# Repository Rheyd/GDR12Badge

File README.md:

# GDR12Badge
GDR Guerra de Robots badge
Now with Pinout Card :D
The GDR12 folder already contains all the example codes up-to-date, this examples will be inmproved over time, and if you spoot a problem please tell me, and also i'll upload more codes, if you have a request, then tell me :D

if you're interested in the procees you can see the post over hackaday, or twitter

https://hackaday.io/project/159659-guerra-de-robots-robots-war-official-badge

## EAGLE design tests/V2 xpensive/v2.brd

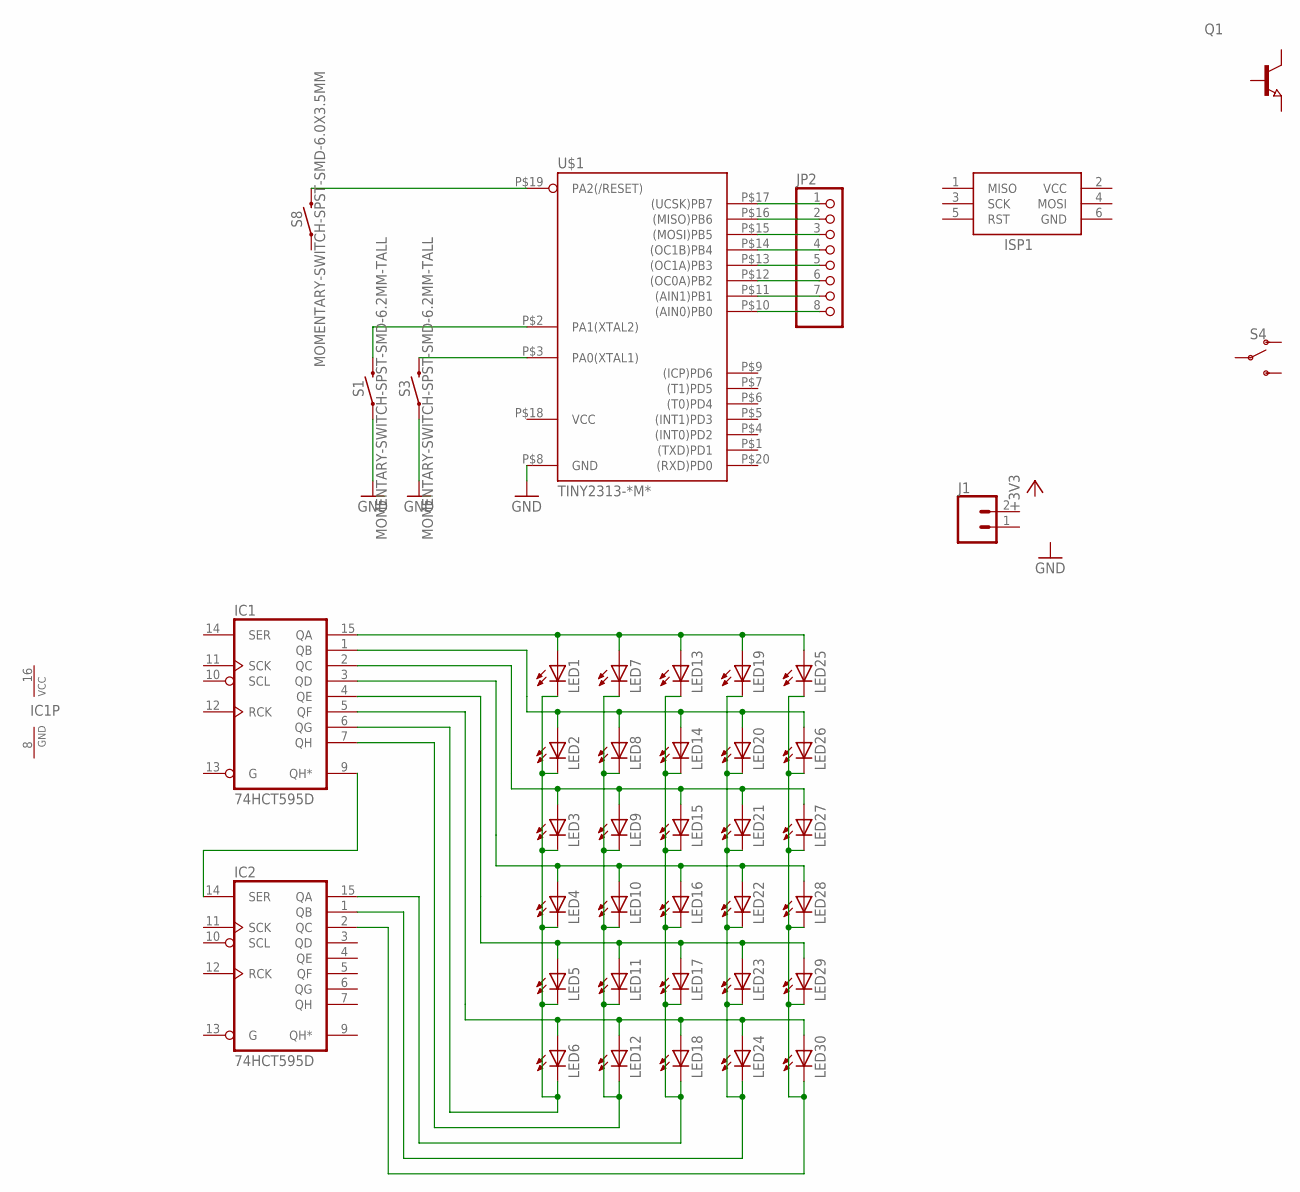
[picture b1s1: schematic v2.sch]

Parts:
IC1, IC2: 74HCT595D; SO16
ISP1: AVRISP-6; AVRISP
J1: CONN_02; 1X02
JP2: PINHD-1X8BIG; 1X08-BIG
LED1, LED2, LED3, LED4, LED5, LED6, LED7, LED8, LED9, LED10, LED11, LED12, LED13, LED14, LED15, LED16, LED17, LED18, LED19, LED20, LED21, LED22, LED23, LED24, LED25, LED26, LED27, LED28, LED29, LED30: LEDCHIPLED_1206; CHIPLED_1206
Q1: NPN-TRANSISTOR_SOT23; SOT23
S1, S3: MOMENTARY-SWITCH-SPST-SMD-6.2MM-TALL; TACTILE_SWITCH_SMD_6.2MM_TALL
S4: SWITCH-SPDT-SMD-RIGHT-ANGLE; SWITCH_SPST_SMD_A
S8: MOMENTARY-SWITCH-SPST-SMD-6.0X3.5MM; TACTILE_SWITCH_SMD_6.0X3.5MM
U$1: TINY2313-*M*; MLF20

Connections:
GND: IC1.8 (GND), IC2.8 (GND), ISP1.6 (GND), S1.A2 (1), S3.A2 (1), U$1.P$8 (GND)
unnamed: JP2.1, U$1.P$17 ((UCSK)PB7)
unnamed: JP2.2, U$1.P$16 ((MISO)PB6)
unnamed: JP2.3, U$1.P$15 ((MOSI)PB5)
unnamed: JP2.4, U$1.P$14 ((OC1B)PB4)
unnamed: JP2.5, U$1.P$13 ((OC1A)PB3)
unnamed: JP2.6, U$1.P$12 ((OC0A)PB2)
unnamed: JP2.7, U$1.P$11 ((AIN1)PB1)
unnamed: JP2.8, U$1.P$10 ((AIN0)PB0)
unnamed: IC1.15 (QA), LED1.A, LED7.A, LED13.A, LED19.A, LED25.A
unnamed: IC1.1 (QB), LED2.A, LED8.A, LED14.A, LED20.A, LED26.A
unnamed: IC1.2 (QC), LED3.A, LED9.A, LED15.A, LED21.A, LED27.A
unnamed: IC1.3 (QD), LED4.A, LED10.A, LED16.A, LED22.A, LED28.A
unnamed: IC1.4 (QE), LED5.A, LED11.A, LED17.A, LED23.A, LED29.A
unnamed: IC1.5 (QF), LED6.A, LED12.A, LED18.A, LED24.A, LED30.A
unnamed: IC1.9 (QH*), IC2.14 (SER)
unnamed: IC1.6 (QG), LED1.C, LED2.C, LED3.C, LED4.C, LED5.C, LED6.C
unnamed: IC1.7 (QH), LED7.C, LED8.C, LED9.C, LED10.C, LED11.C, LED12.C
unnamed: IC2.15 (QA), LED13.C, LED14.C, LED15.C, LED16.C, LED17.C, LED18.C
unnamed: IC2.1 (QB), LED19.C, LED20.C, LED21.C, LED22.C, LED23.C, LED24.C
unnamed: IC2.2 (QC), LED25.C, LED26.C, LED27.C, LED28.C, LED29.C, LED30.C
unnamed: S3.B2 (2), U$1.P$3 (PA0(XTAL1))
unnamed: S1.B2 (2), U$1.P$2 (PA1(XTAL2))
unnamed: S8.2, U$1.P$19 (PA2(/RESET))
VCC: IC1.16 (VCC), IC2.16 (VCC), ISP1.2 (VCC), U$1.P$18 (VCC)

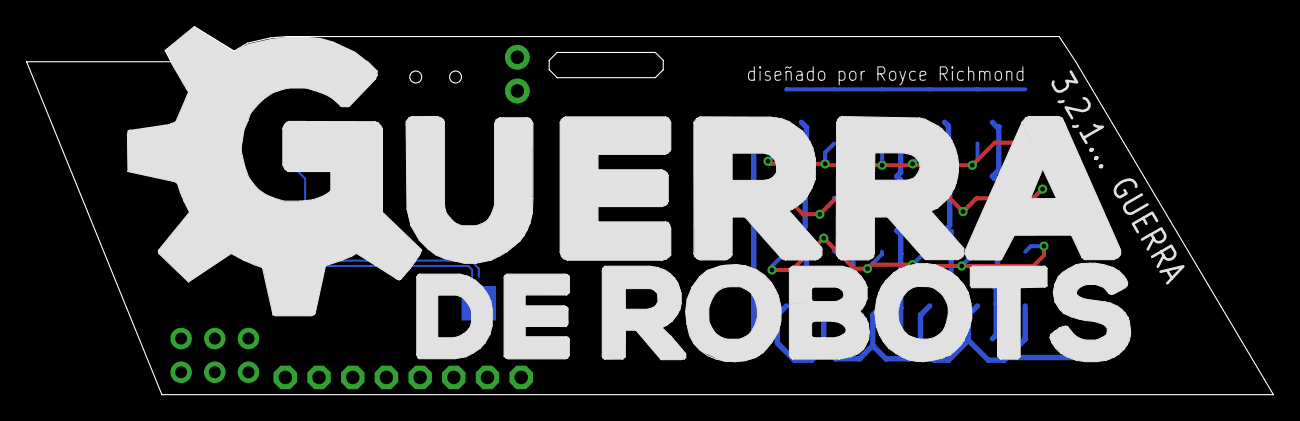
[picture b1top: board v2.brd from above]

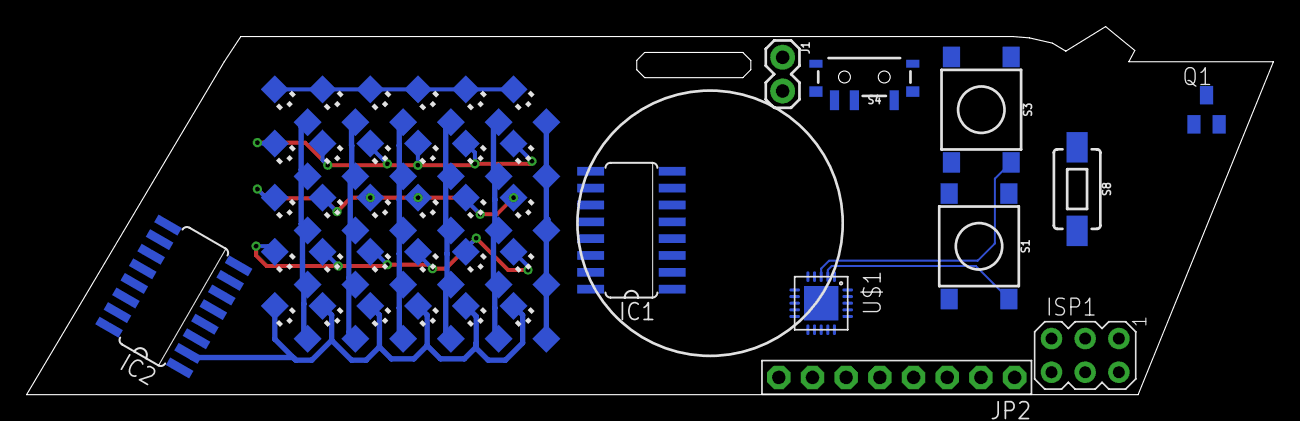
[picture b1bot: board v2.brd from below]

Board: 2 copper layers, 94.0 x 27.8 mm, 41 parts (41 on the bottom side), 25 nets.

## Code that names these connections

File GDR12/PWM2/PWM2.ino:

#include <avr/interrupt.h>
int temir=0,a=0,rep=0;
uint8_t bits=0,state=4;
ISR(TIMER1_CAPT_vect){
  a++;
  switch (state){
  case 0://startuptime
  if(a>=97){
    TCCR1A&=~(1<<COM1B1);
    state=1;
    a=0;
  }
  else{
    TCCR1A|=(1<<COM1B1);
    state=0;
  }
  break;
  case 1://off time of the startuptime
  if(a>=25){
    TCCR1A|=(1<<COM1B1);
    state=2;
    a=0;
  }
  break; 
  case 2://cero and one evaluation time
  TCCR1A|=(1<<COM1B1);//enable the output PWM
  if((0x800&temir)==0x800){
    if(a>=49){
      temir=temir<<1;
      state=3;
      a=0;
      bits++;
    }    
  }
  else{
    if(a>=25){
      temir=temir<<1;
      state=3;
      a=0;
      bits++;
    }    
  }

  break;
  case 3://off time
  if(bits<=11){
    TCCR1A&=~(1<<COM1B1);
    if(a>=25){
      state=2;
      a=0;
    }
  }
  else
    state=4;
  break;
  case 4://off time
    TCCR1A&=~(1<<COM1B1);
    a=0;
  /*  if(a>=1801 & rep<=3){
      state=0;
      a=0;
      rep++;
    } 
    else{
    state=4;
    }*/
  break;
  }
}
void setup() {
  //40Khz PWM for the IR sony rptocol, library in progress
  TCCR1A=0;//clear registers just in case
  TCCR1B=0;//clear registers just in case
  //TCCR1A|=(1<<COM1B1);
  /*
  Clear OC1A/OC1B on Compare Match when upcounting.
  Set OC1A/OC1B on Compare Match
  when downcounting
  */
  TCCR1B|=(1<<WGM13)|(1<<CS10);//clock selection and output mode
  ICR1=100;//new top definition
  DDRB|=(1<<PB4);//output definition
  OCR1B=33;//compare value, where 100 is 100 dutycyle, 1/3 for the sony IR protocol
  TIMSK|=(1<<ICIE1);//enable the interrupt when top value (ICR1) is reached
        sei();
  /*
  the Timer/Counter1 Input Capture interrupt is enabled. The corresponding Interrupt
  Vector
  */
  PORTA|=((1<<PA1)|(1<<PA0));//Input pullup declaration
  PORTB&=~((1<<PB5)|(1<<PB5)|(1<<PB6));//Input pullup declaration  
  DDRB|=((1<<PB5)|(1<<PB5)|(1<<PB6));
  TCCR1A&=~(1<<COM1B1);
  
}
void loop() {
    if((PINA&0X02)!=0X02){//run PA1
      temir=0b001101101111;
      state=0;
      a=0;
      TCCR1A|=(1<<COM1B1);
    }
    else if((PINA&0X01)!=0X01){//stop PA0
      temir=0b111100001111;
      state=0;
      a=0;
      TCCR1A|=(1<<COM1B1);      
    }
}

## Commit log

2018-08-30 Add files via upload
    example codes
    the codes that have a library in the name, have already been converted to a standard Arduino library for usage, other codes rely on bit and port manipulation, this example codes will be updated and d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
    i hope that you enjoy playing with this, as much as i did.

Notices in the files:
parts and their libraries:
SparkFun-Switches: Licensing: Creative Commons ShareAlike 4.0 International - https://creativecommons.org/licenses/by-sa/4.0
